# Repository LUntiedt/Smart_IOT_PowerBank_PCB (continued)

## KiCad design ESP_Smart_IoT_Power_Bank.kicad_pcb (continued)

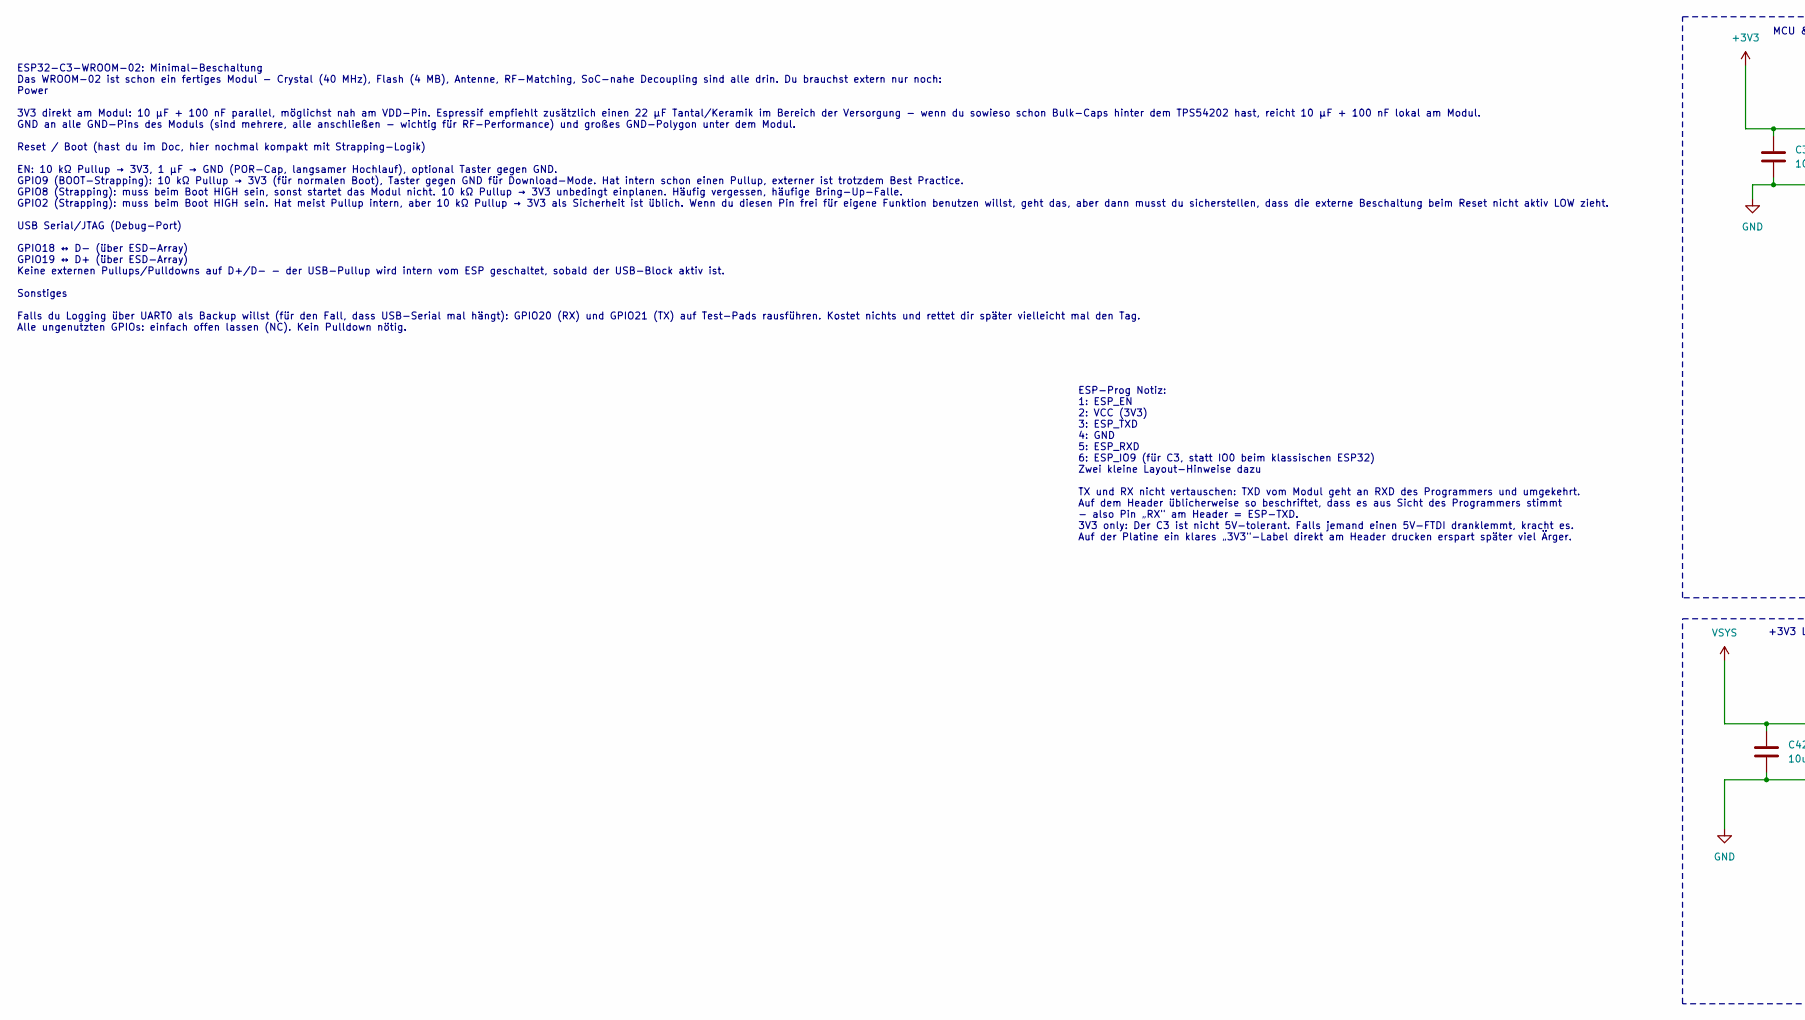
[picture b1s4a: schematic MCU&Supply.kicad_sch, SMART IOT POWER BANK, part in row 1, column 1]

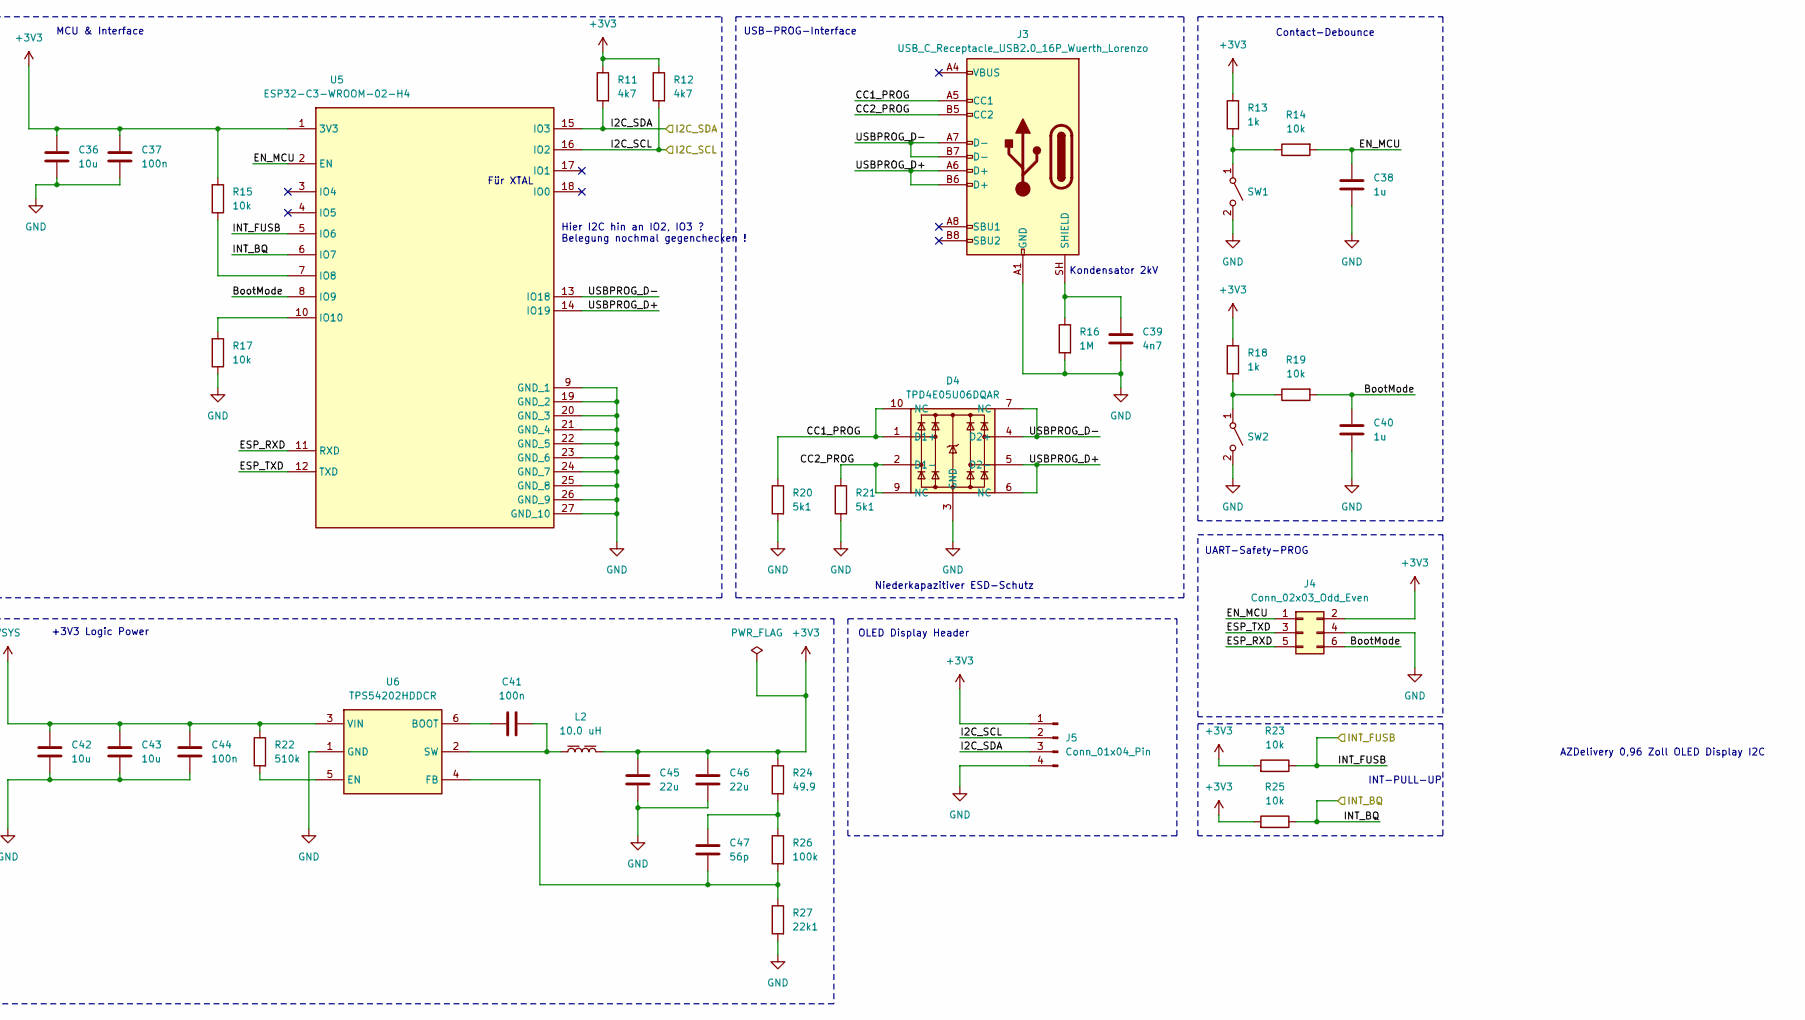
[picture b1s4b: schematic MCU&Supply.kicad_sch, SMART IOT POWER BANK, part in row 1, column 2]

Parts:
C36, C42, C43: 10u; C_Wurth_WCAP-CSGP-1206_H1.6; Voltage 25.0; Part Number 885012208069
C37, C41, C44: 100n; C_Wurth_WCAP-CSGP-0402; Voltage 50.0; Part Number 885012205086
C38, C40: 1u; C_Wurth_WCAP-CSGP-1206_H1.6; Voltage 50.0; Part Number 885012208093
C39: 4n7; C_Wurth_WCAP-CSGP-0402; Voltage 50.0; Part Number 885012205065
C45, C46: 22u; C_Wurth_WCAP-CSGP-1206_H1.6; Voltage 16.0; Part Number 885012108018
C47: 56p; C_Wurth_WCAP-CSGP-0402; Mouser Part Number 77-VJ0402A560JXAAC
D4: TPD4E05U06DQAR; DQA_R-PUSON-N10_; Mouser Part Number 595-TPD4E05U06DQAR
J3: USB_C_Receptacle_USB2.0_16P_Wuerth_Lorenzo; 629722000214; Manufacturer_Part_Number 629722000214
J4: Conn_02x03_Odd_Even; PinHeader_2x03_P2.54mm_Vertical
J5: Conn_01x04_Pin; PinHeader_1x04_P2.54mm_Vertical
L2: 10.0 uH; L_Wurth_WE-LHMI-7050; Part Number 74437349100
R11, R12: 4k7; R_Wurth_WRIS-RSKS-0402; Part Number 560112110245
R13, R18: 1k; R_Wurth_WRIS-RSKS-0402; Part Number 560112110012
R14, R15, R17, R19, R23, R25: 10k; R_Wurth_WRIS-RSKS-0402; Part Number 560112110020
R16: 1M; R_Wurth_WRIS-RSKS-0402; Part Number 560112110033
R20, R21: 5k1; R_Wurth_WRIS-RSKS-0402; Manufacturer_Part_Number ERJ2RKF5101X
R22: 510k; R_Wurth_WRIS-RSKS-0402; Manufacturer_Part_Number ERJ-U02F5103X
R24: 49.9; R_Wurth_WRIS-RSKS-0402; Part Number 560112110002
R26: 100k; R_Wurth_WRIS-RSKS-0402; Part Number 560112110019
R27: 22k1; R_Wurth_WRIS-RSKS-0402; Part Number 560112110099
SW1, SW2: 434121025816; SW_Wurth_WS-TASV_434121025816; Part Number 434121025816
U5: ESP32-C3-WROOM-02-H4; ESP32C3WROOM02H4; Mouser Part Number 356-ESP32C3WROOM02H4
U6: TPS54202HDDCR; SOT95P280X110-6N; Mouser Part Number 595-TPS54202HDDCR

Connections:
+3V3: C36.1, C37.1, C45.2, C46.2, J4.2, J5.1, L2.2, R11.2, R12.2, R13.2, R15.1, R18.2, R23.1, R24.2, R25.1, U5.1 (3V3); also elsewhere on the board
/Charge_Controller/~INT: R25.2, U5.6 (IO7); also elsewhere on the board
/MCU&Supply/BootMode: C40.1, J4.6, R19.1, U5.8 (IO9)
/MCU&Supply/CC1_PROG: D4.1 (D1+), D4.10 (NC), J3.A5 (CC1), R20.2
/MCU&Supply/CC2_PROG: D4.2 (D1-), D4.9 (NC), J3.B5 (CC2), R21.2
/MCU&Supply/EN_MCU: C38.1, J4.1, R14.1, U5.2 (EN)
/MCU&Supply/ESP_RXD: J4.5, U5.11 (RXD)
/MCU&Supply/ESP_TXD: J4.3, U5.12 (TXD)
/MCU&Supply/I2C_SCL: J5.2, R12.1, U5.16 (IO2); also elsewhere on the board
/MCU&Supply/I2C_SDA: J5.3, R11.1, U5.15 (IO3); also elsewhere on the board
/MCU&Supply/INT_FUSB: R23.2, U5.5 (IO6); also elsewhere on the board
/MCU&Supply/USBPROG_D+: D4.5 (D2-), D4.6 (NC), J3.A6 (D+), J3.B6 (D+), U5.14 (IO19)
/MCU&Supply/USBPROG_D-: D4.4 (D2+), D4.7 (NC), J3.A7 (D-), J3.B7 (D-), U5.13 (IO18)
GND: C36.2, C37.2, C38.2, C39.2, C40.2, C42.2, C43.2, C44.2, C45.1, C46.1, D4.3 (GND), D4.8 (GND), J3.A1 (GND), J4.4, J5.4, R16.1, R17.2, R20.1, R21.1, R27.1, SW1.2 (B), SW2.2 (B), U5.9 (GND_1), U5.19 (GND_2), U5.20 (GND_3), U5.21 (GND_4), U5.22 (GND_5), U5.23 (GND_6), U5.24 (GND_7), U5.25 (GND_8), U5.26 (GND_9), U5.27 (GND_10), U6.1 (GND); also elsewhere on the board
unnamed: C47.1, R24.1, R26.2
unnamed: C39.1, J3.SH (SHIELD), R16.2
unnamed: R13.1, R14.2, SW1.1 (A)
unnamed: R18.1, R19.2, SW2.1 (A)
unnamed: R15.2, U5.7 (IO8)
unnamed: R17.1, U5.10 (IO10)
unnamed: C41.1, U6.6 (BOOT)
unnamed: R22.1, U6.5 (EN)
unnamed: C47.2, R26.1, R27.2, U6.4 (FB)
unnamed: C41.2, L2.1, U6.2 (SW)
VSYS: C42.1, C43.1, C44.1, R22.2, U6.3 (VIN); also elsewhere on the board

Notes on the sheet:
Hier I2C hin an IO2, IO3 ? Belegung nochmal gegenchecken !
USB-PROG-Interface
UART-Safety-PROG
+3V3 Logic Power
Kondensator 2kV
OLED Display Header
MCU & Interface
AZDelivery 0,96 Zoll OLED Display I2C
ESP-Prog Notiz: 1: ESP_EN 2: VCC (3V3) 3: ESP_TXD 4: GND 5: ESP_RXD 6: ESP_IO9 (für C3, statt IO0 beim klassischen ESP32) Zwei kleine Layout-Hinweise dazu TX und RX nicht vertauschen: TXD vom Modul geht an RXD des Programmers und umgekehrt. Auf dem Header üblicherweise so beschriftet, dass es aus S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
INT-PULL-UP
ESP32-C3-WROOM-02: Minimal-Beschaltung Das WROOM-02 ist schon ein fertiges Modul - Crystal (40 MHz), Flash (4 MB), Antenne, RF-Matching, SoC-nahe Decoupling sind alle drin. Du brauchst extern nur noch: Power 3V3 direkt am Modul: 10 µF + 100 nF parallel, möglichst nah am VDD-Pin. Espressif empfiehlt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
Für XTAL
Niederkapazitiver ESD-Schutz
Contact-Debounce

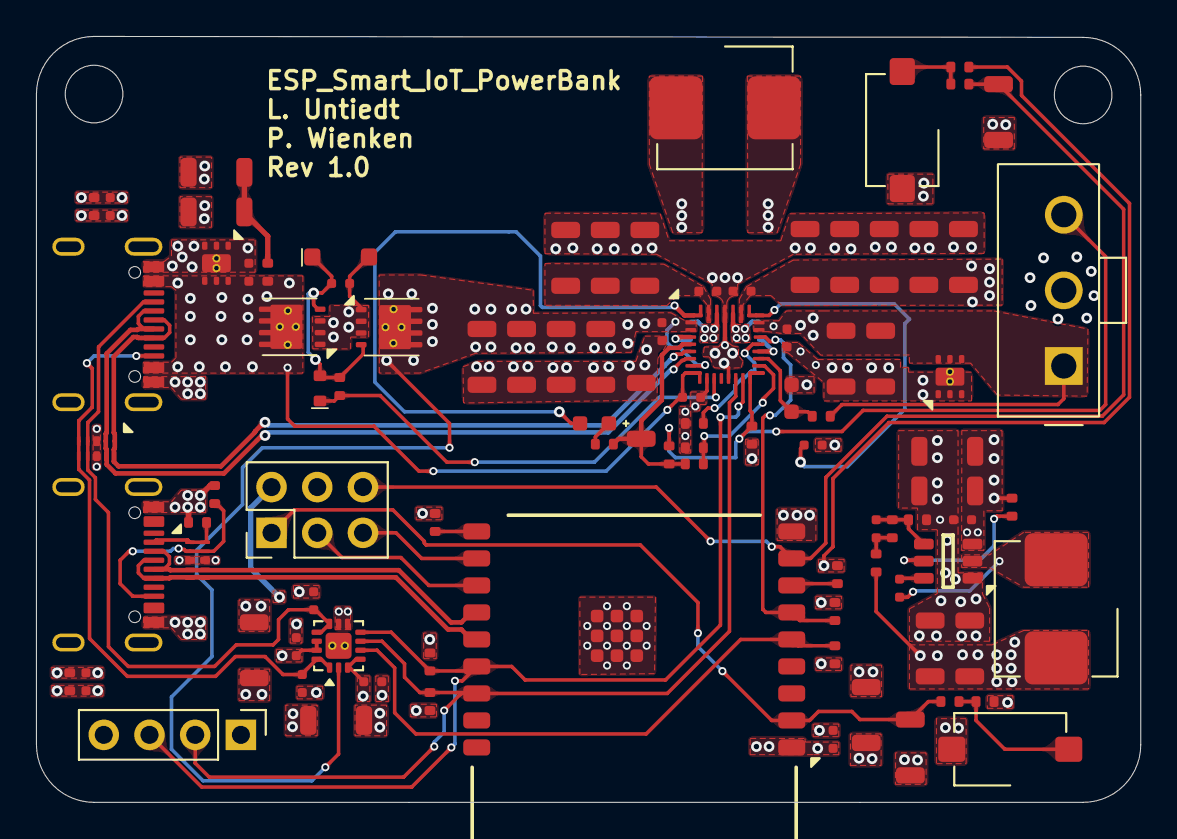
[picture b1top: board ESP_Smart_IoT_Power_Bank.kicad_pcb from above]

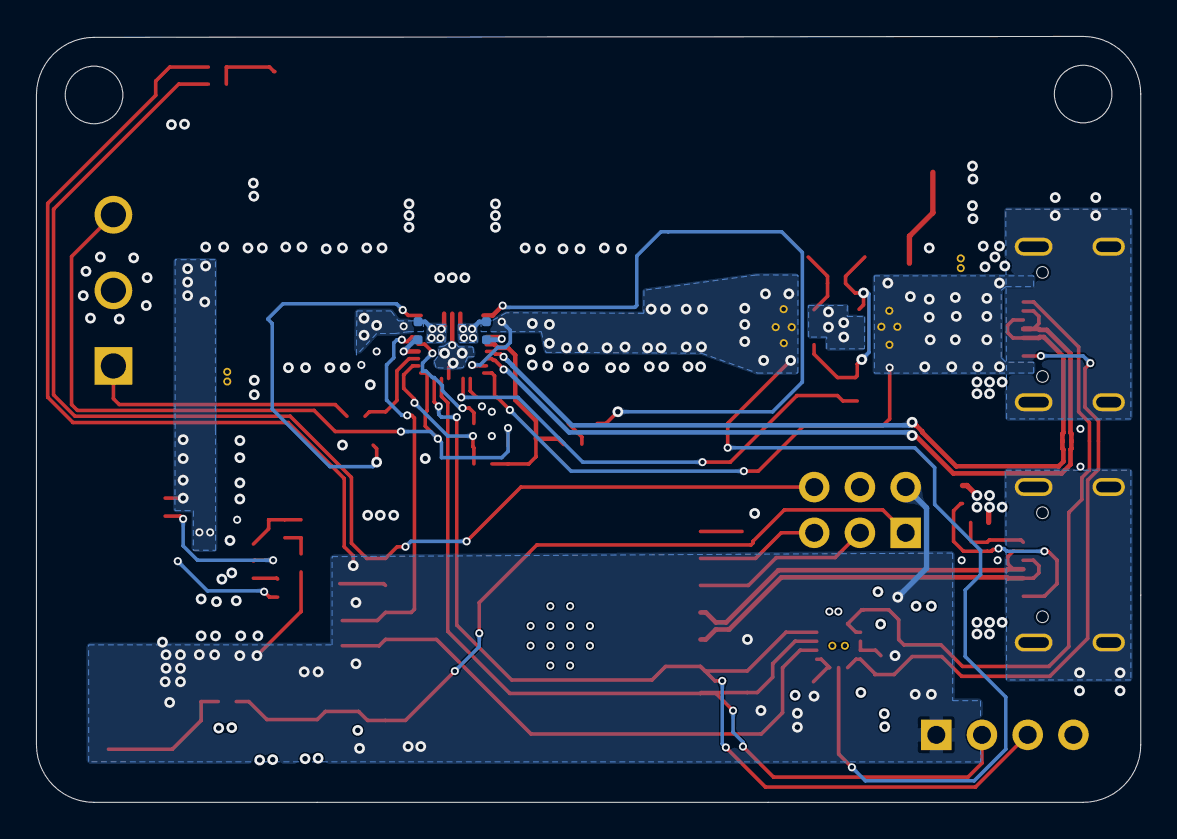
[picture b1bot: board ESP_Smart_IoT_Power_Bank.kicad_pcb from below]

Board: 4 copper layers, 61.4 x 42.5 mm, 98 parts (2 on the bottom side), 50 nets.

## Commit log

2026-06-07 Updated Files
2026-06-21 Revise inductor values for U3 and U6 components
    Updated inductor specifications for U3 and U6 in the Power Path section.
2026-06-21 Revise thermal management section in README
    Updated thermal management guidelines to emphasize high power rails and via distribution.
